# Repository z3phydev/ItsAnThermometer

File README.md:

# ItsAnThermometer
Its a simple Thermometer... what did you expect. It has 3 leds for tempature (under 20 for blue, 20-24 for green and over 24 for red. But can be changed) powered but a XIAO RP2040
## How to use
1. Build it
2. Flash circutpython to the XIAO
3. Upload main.py to it
4. Plug in or add 4x AA batteries
6. Observe

You can use the toggle switch to change the power source

## Why did I make it
I was sick so I was off school and had 2 days to make something and I needed one. Also it is to show my little brother eletronics.

## Schematic

## PCB

## 3D Model

## BOM

|Reference(s)|Qty|Value/Description             |MFR                         |MFR No.        |Mouser No.         |Unit Price GBP    |Total Price GBP|Link                                                                                                           |FIELD10            |FIELD11               |FIELD12        |
|------------|---|------------------------------|----------------------------|---------------|-------------------|------------------|---------------|---------------------------------------------------------------------------------------------------------------|-------------------|----------------------|---------------|
|~           |5  |PCB and Partial assebly       |JLCPCB                      |~              |~                  |~                 |2.46           |https://jlcpcb.com/                                                                                            |                   |                      |               |
|U2          |1  |Seeed XIAO RP2040 with Headers|Raspberry Pi                |102010630      |713-102010630      |3.9               |3.9            |https://www.mouser.co.uk/ProductDetail/Seeed-Studio/102010630?qs=sqEgtWRSLJ0HHL%252BkmwiGyA%3D%3D              |                   |                      |               |
|U1          |1  |LM35 Temp sensor              |Texas Instruments           |LM35DZ/LFT1    |926-LM35DZ/LFT1    |1.26              |1.26           |https://www.mouser.co.uk/ProductDetail/Texas-Instruments/LM35DZ-LFT1?qs=QbsRYf82W3H30AtKgrS0IA%3D%3D           |                   |                      |               |
|BT1         |1  |4x AA Battey Holder           |Keystone Electronics        |2477           |534-2477           |1.6               |1.6            |https://www.mouser.co.uk/ProductDetail/Keystone-Electronics/2477?qs=Q3RoVmURDolEbXnNenQutg%3D%3D               |                   |                      |               |
|R2, R3      |2  |10ohm resistor                |YAGEO                       |MF0207FTE52-75R|603-MF0207FTE52-75R|0.08              |0.16           |https://www.mouser.co.uk/ProductDetail/YAGEO/MF0207FTE52-10R?qs=Is6ZsIPfHkZVWUebLBVbaw%3D%3D                   |                   |                      |               |
|R1          |1  |75ohm resistor                |YAGEO                       |MF0207FTE52-75R|603-MF0207FTE52-75R|0.08              |0.08           |https://www.mouser.co.uk/ProductDetail/YAGEO/MF0207FTE52-75R?qs=KUIzHt%2Fe91nXiKietXMfvA%3D%3D                 |                   |                      |               |
|SW1         |1  |SPDT Switch                   |E-Switch                    |100SP1T1B4M2QE |612-100-A1421      |1.97              |1.97           |https://www.mouser.co.uk/ProductDetail/E-Switch/100SP1T1B4M2QE?qs=YXf4ACKMM4xJ0mJK%2FyIa1g%3D%3D               |                   |                      |               |
|J1          |1  |USB A Port                    |Molex                       |67643-0910     |538-67643-0910     |1.12              |1.12           |https://www.mouser.co.uk/ProductDetail/Molex/67643-0910?qs=EuyFtE1skifNhj6pwWTsXw%3D%3D                        |                   |                      |               |
|C1          |1  |100nF Capacitor               |Vishay / BC Components      |K104K15X7RF5WH5|594-K104K15X7RF5WH5|0.17              |0.17           |https://www.mouser.co.uk/ProductDetail/Vishay-BC-Components/K104K15X7RF5WH5?qs=8fb2TFeI5qGYDjl7%252BWZxcg%3D%3D|                   |                      |               |
|D4, D5      |2  |Schottky Diode                |Vishay General Semiconductor|SB140-E3/73    |625-SB140-E3/73    |0.14              |0.28           |https://www.mouser.co.uk/ProductDetail/Vishay-General-Semiconductor/SB140-E3-73?qs=u91jd7aysvPpl5oKH36UtQ%3D%3D|                   |                      |               |
|U3          |1  |AMS1117-3.3 Breakout Board    |Texas Instruments           |~              |~                  |1.26              |1.26           |https://www.aliexpress.com/item/1005007091283048.html                                                          |                   |                      |               |
|D1, D2, D3  |3  |Coloured LEDs                 |~                           |~              |~                  |(In a 450pcs pack)|0.76           |https://www.aliexpress.com/item/1005008664239729.html                                                          |                   |                      |               |
|~           |2  |Screw 6 mm M3                 |RND                         |610-00421      |~                  |(In 200pcs pack)  |0.74           |https://uk.rs-online.com/web/p/machine-screws/0492499                                                          |                   |                      |               |
|~           |1  |10cm x 10cm MDF 12mm Thick    |MEDITE                      |~              |~                  |2                 |2              |https://www.cutmy.co.uk/wood/mdf-board/standard/12mm/L100-W100/                                                |                   |                      |               |
|            |   |                              |                            |               |                   |                  |               |                                                                                                               |                   |                      |               |
|            |   |                              |                            |               |                   |                  |               |                                                                                                               |                   |Total Price USD approx|Total Price GBP|
|            |   |                              |                            |               |                   |                  |               |                                                                                                               |Items              |23.7                  |17.76          |
|            |   |                              |                            |               |                   |                  |               |                                                                                                               |Shipping (and fees)|24.72                 |18.52          |
|            |   |                              |                            |               |                   |                  |               |                                                                                                               |Final              |48.42                 |36.28          |

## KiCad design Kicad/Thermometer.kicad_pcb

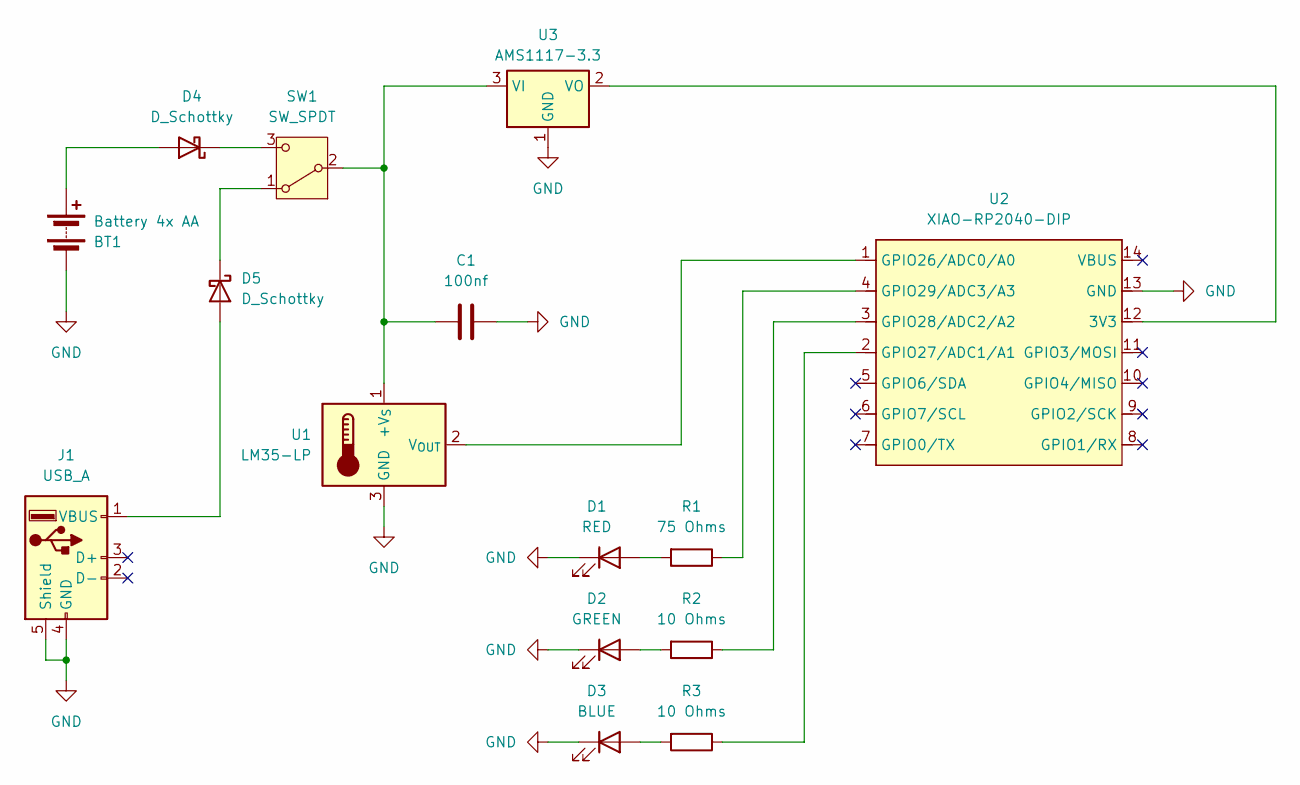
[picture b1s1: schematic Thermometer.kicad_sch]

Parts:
BT1: Battery 4x AA; BAT_2477
C1: 100nf; C_Disc_D4.3mm_W1.9mm_P5.00mm
D1: RED; LED_D5.0mm
D2: GREEN; LED_D5.0mm
D3: BLUE; LED_D5.0mm
D4, D5: D_Schottky; D_DO-41_SOD81_P10.16mm_Horizontal
J1: USB_A; USB_A_Molex_67643_Horizontal
R1: 75 Ohms; R_Axial_DIN0207_L6.3mm_D2.5mm_P10.16mm_Horizontal
R2, R3: 10 Ohms; R_Axial_DIN0207_L6.3mm_D2.5mm_P10.16mm_Horizontal
SW1: SW_SPDT; SW_100SP1T1B4M2QE
U1: LM35-LP; TO-92_Wide
U2: XIAO-RP2040-DIP
U3: AMS1117-3.3; AMS1117Breakout

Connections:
GND: BT1.N (-), C1.2, D1.1 (K), D2.1 (K), D3.1 (K), J1.4 (GND), J1.5 (Shield), U1.3 (GND), U2.13 (GND), U3.1 (GND)
unnamed: BT1.P (+), D4.2 (A)
unnamed: D1.2 (A), R1.2
unnamed: D2.2 (A), R2.2
unnamed: D3.2 (A), R3.2
unnamed: D4.1 (K), SW1.3 (C)
unnamed: D5.2 (A), J1.1 (VBUS)
unnamed: D5.1 (K), SW1.1 (A)
unnamed: C1.1, SW1.2 (B), U1.1 (+V_{S}), U3.3 (VI)
unnamed: U1.2 (V_{OUT}), U2.1 (GPIO26/ADC0/A0)
unnamed: U2.12 (3V3), U3.2 (VO)
unnamed: R3.1, U2.2 (GPIO27/ADC1/A1)
unnamed: R2.1, U2.3 (GPIO28/ADC2/A2)
unnamed: R1.1, U2.4 (GPIO29/ADC3/A3)

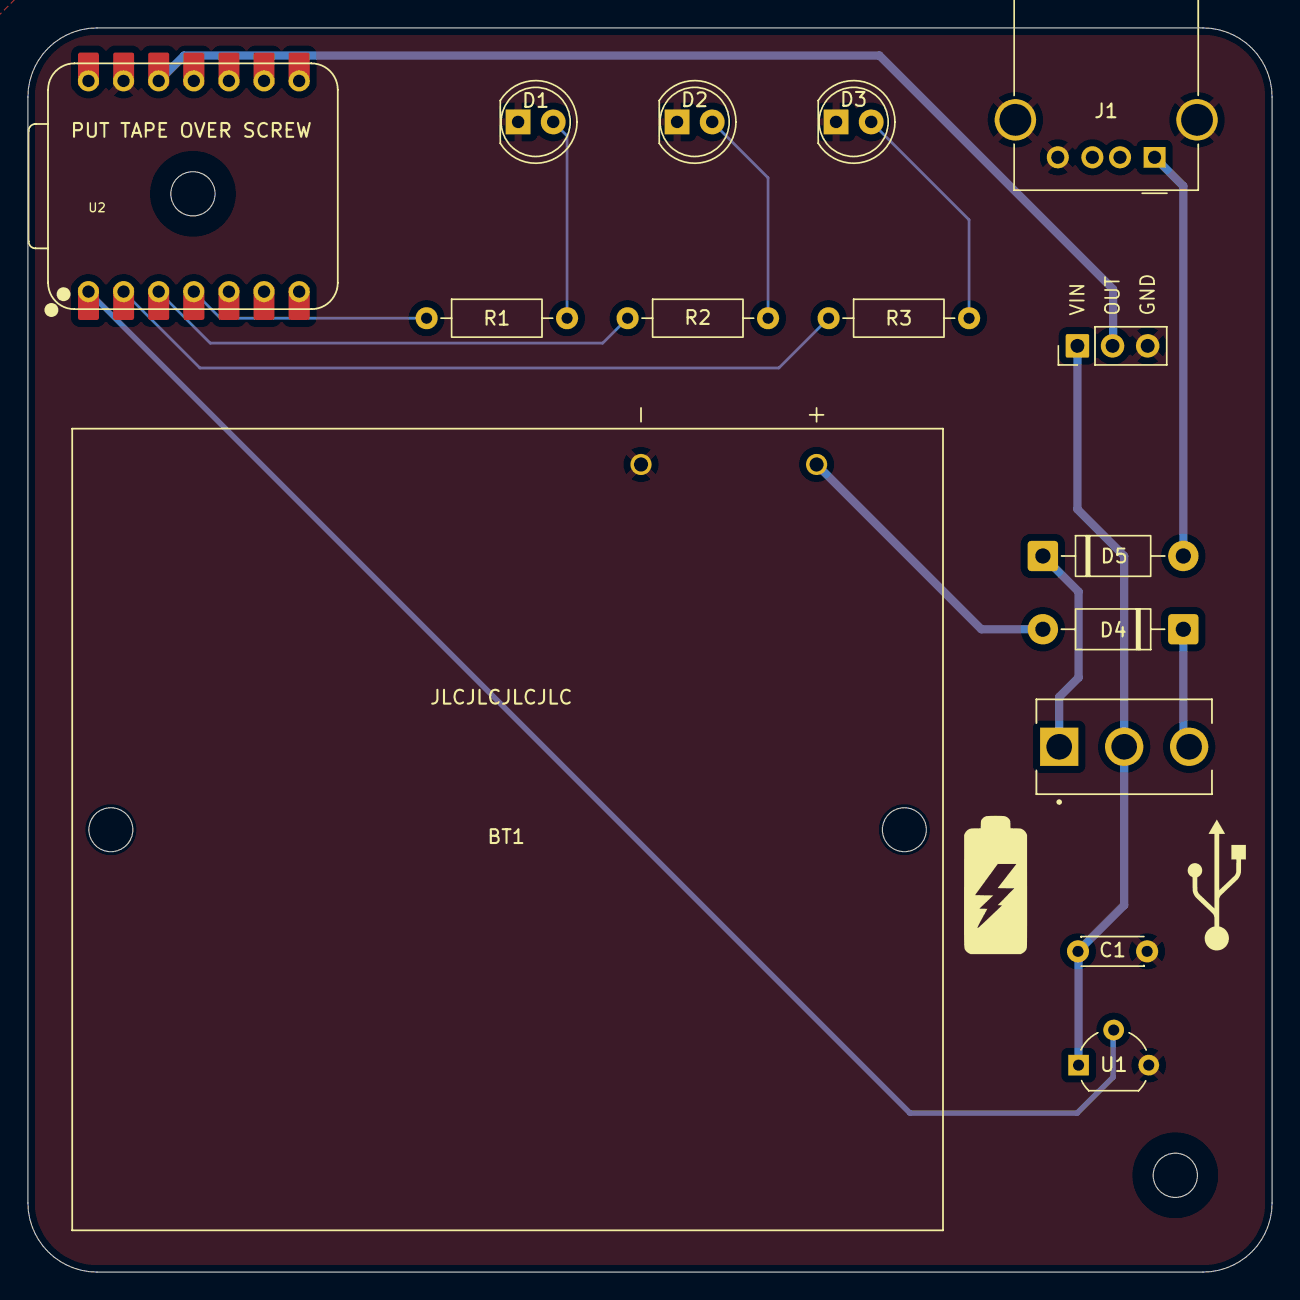
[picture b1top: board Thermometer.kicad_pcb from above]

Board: 2 copper layers, 90.0 x 90.0 mm, 15 parts (0 on the bottom side), 14 nets.

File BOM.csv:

Reference(s),Qty,Value/Description,MFR,MFR No.,Mouser No.,Unit Price GBP,Total Price GBP,Link,,,
~,5,PCB and Partial assebly,JLCPCB,~,~,~,2.46,https://jlcpcb.com/,,,
U2,1,Seeed XIAO RP2040 with Headers,Raspberry Pi,102010630,713-102010630,3.9,3.9,https://www.mouser.co.uk/ProductDetail/Seeed-Studio/10201063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,,,
U1,1,LM35 Temp sensor,Texas Instruments,LM35DZ/LFT1,926-LM35DZ/LFT1,1.26,1.26,https://www.mouser.co.uk/ProductDetail/Texas-Instruments/LM3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,,,
BT1,1,4x AA Battey Holder,Keystone Electronics,2477,534-2477,1.6,1.6,https://www.mouser.co.uk/ProductDetail/Keystone-Electronics/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,,,
"R2, R3",2,10ohm resistor,YAGEO,MF0207FTE52-75R,603-MF0207FTE52-75R,0.08,0.16,https://www.mouser.co.uk/ProductDetail/YAGEO/MF0207FTE52-10R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,,,
R1,1,75ohm resistor,YAGEO,MF0207FTE52-75R,603-MF0207FTE52-75R,0.08,0.08,https://www.mouser.co.uk/ProductDetail/YAGEO/MF0207FTE52-75R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,,,
SW1,1,SPDT Switch,E-Switch,100SP1T1B4M2QE,612-100-A1421,1.97,1.97,https://www.mouser.co.uk/ProductDetail/E-Switch/100SP1T1B4M2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,,,
J1,1,USB A Port,Molex,67643-0910,538-67643-0910,1.12,1.12,https://www.mouser.co.uk/ProductDetail/Molex/67643-0910?qs=E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,,,
C1,1,100nF Capacitor,Vishay / BC Components,K104K15X7RF5WH5,594-K104K15X7RF5WH5,0.17,0.17,https://www.mouser.co.uk/ProductDetail/Vishay-BC-Components/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,,,
"D4, D5",2,Schottky Diode,Vishay General Semiconductor,SB140-E3/73,625-SB140-E3/73,0.14,0.28,https://www.mouser.co.uk/ProductDetail/Vishay-General-Semico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,,,
U3,1,AMS1117-3.3 Breakout Board,Texas Instruments,~,~,1.26,1.26,https://www.aliexpress.com/item/1005007091283048.html,,,
"D1, D2, D3",3,Coloured LEDs,~,~,~,(In a 450pcs pack),0.76,https://www.aliexpress.com/item/1005008664239729.html,,,
~,2,Screw 6 mm M3,RND,610-00421,~,(In 200pcs pack),0.74,https://uk.rs-online.com/web/p/machine-screws/0492499,,,
~,1,10cm x 10cm MDF 12mm Thick,MEDITE,~,~,2,2,https://www.cutmy.co.uk/wood/mdf-board/standard/12mm/L100-W100/,,,
,,,,,,,,,,,
,,,,,,,,,,Total Price USD approx,Total Price GBP
,,,,,,,,,Items,23.7,17.76
,,,,,,,,,Shipping (and fees),24.72,18.52
,,,,,,,,,Final,48.42,36.28

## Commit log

2026-03-12 Revise README with project details and instructions
    Updated project name and added usage instructions, schematic, PCB, 3D model images, and BOM section.
2026-03-12 Create PLACEHOLDER
2026-03-12 Create WRL
2026-03-12 Create Production
2026-03-12 Implement temperature-based LED control in main.py
2026-03-13 Update 3D model images in README
